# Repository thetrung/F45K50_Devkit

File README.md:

PIC18-F45K50-DevKit / Mini-USB
===================================
Basic USB Type-B DevKit I made to learn about **PIC18F45K50** microcontroller.

- **PIC18F45K50-I/MV** will be used specifically as UQFN-40(5x5) instead DIP-40 package in previous THT version.

I actually tried to put all SMD components on front side only. Used Mini-USB instead of USB-B in previous THT version. So this isn't optimized by any mean, just simply a practice to experience what SMD PCB Design look like & what challenge compare to THT ? Although initial goal was same size to a DIP-40. But Port hints are so valuable to remove.

### 1. Basic functionality :
- USB-powered 5V supply.
- USB-HID controllable with PIC18F45k50 with D+/D- pins.
- Reset Button -> Trigger MLCR-pin pull-down -> GND.
- Programming/Debugging with PICKIT-3 via ICSP pins.
- 5 pluggable PORTS : RA, RB, RC, RD, RE.
- LED at RD0 for Blink Test.

### NOTE :
- Fixed critical issues on MCLR pin, Reset Button, ICSP..
- Should only take this design as references to parts.
- No longer update/fix bugs anymore as I move-on to new designs ( with less flaws ).

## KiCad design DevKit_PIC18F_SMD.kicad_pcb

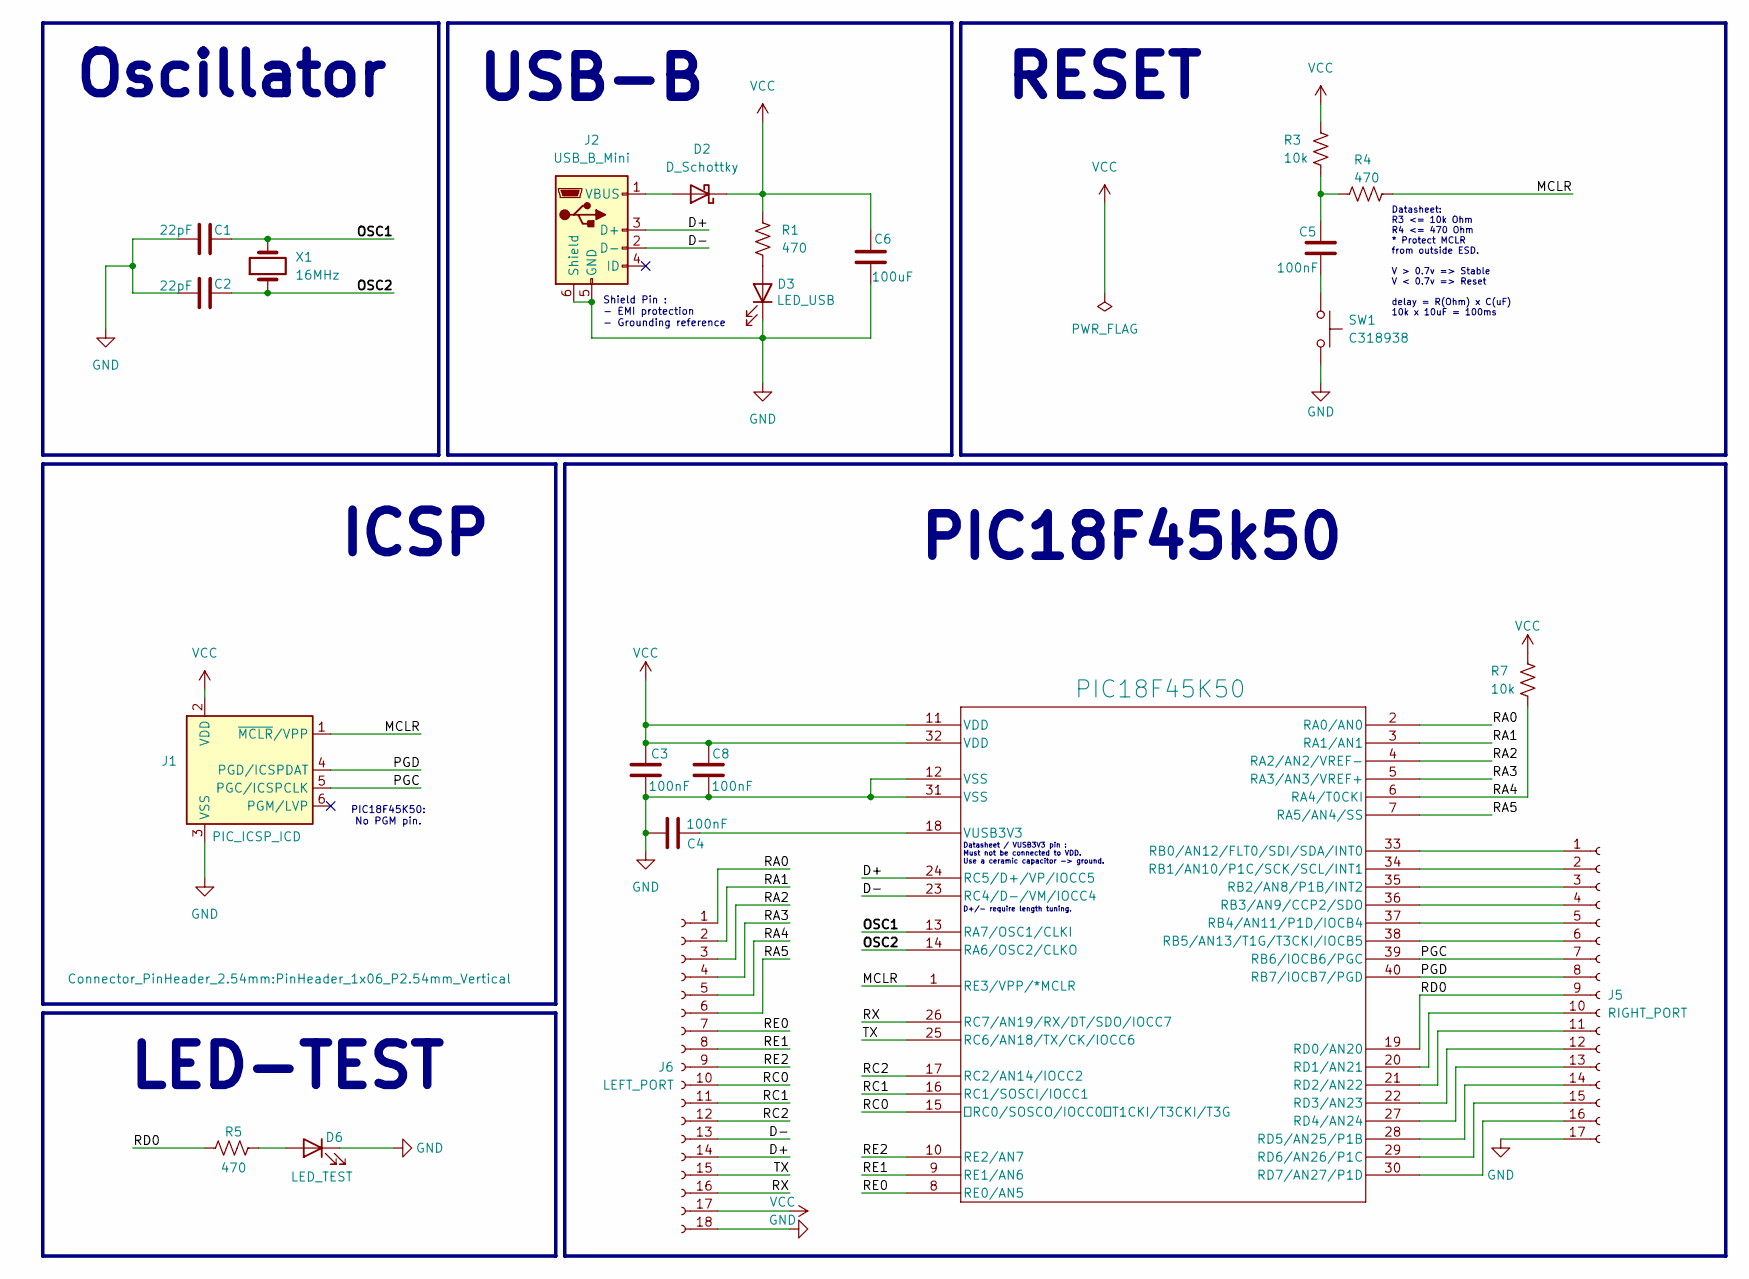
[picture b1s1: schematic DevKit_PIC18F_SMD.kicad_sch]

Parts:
C1, C2: 22pF; C_0805_2012Metric
C3, C4, C5, C8: 100nF; C_1206_3216Metric
C6: 100uF; C_1206_3216Metric
D2: D_Schottky; D_0603_1608Metric
D3: LED_USB; LED_0805_2012Metric
D6: LED_TEST; LED_0805_2012Metric
J1: PIC_ICSP_ICD; PinHeader_1x06_P2.54mm_Vertical
J2: USB_B_Mini; USB_Mini-B_Tensility_54-00023_Vertical
J5: RIGHT_PORT; PinHeader_1x17_P2.54mm_Vertical
J6: LEFT_PORT; PinHeader_1x18_P2.54mm_Vertical
PIC18F45K50: PIC18F45K50-I/MV; QFN-40-1EP_5x5mm_P0.4mm_EP3.6x3.6mm
R1, R4, R5: 470; R_0805_2012Metric
R3, R7: 10k; R_1206_3216Metric
SW1: C318938; SW_SPST_SKQG_WithStem
X1: 16MHz; Crystal_SMD_2520-4Pin_2.5x2.0mm

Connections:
/D+: J2.3 (D+), J6.14, PIC18F45K50.24 (RC5/D+/VP/IOCC5)
/D-: J2.2 (D-), J6.13, PIC18F45K50.23 (RC4/D-/VM/IOCC4)
/MCLR: J1.1 (~MCLR/VPP), PIC18F45K50.1 (RE3/VPP/*MCLR), R4.1
/OSC1: C1.1, PIC18F45K50.13 (RA7/OSC1/CLKI), X1.2
/OSC2: C2.1, PIC18F45K50.14 (RA6/OSC2/CLKO), X1.1
/PGC: J1.5 (PGC/ICSPCLK), J5.7, PIC18F45K50.39 (RB6/IOCB6/PGC)
/PGD: J1.4 (PGD/ICSPDAT), J5.8, PIC18F45K50.40 (RB7/IOCB7/PGD)
/RA0: J6.1, PIC18F45K50.2 (RA0/AN0)
/RA1: J6.2, PIC18F45K50.3 (RA1/AN1)
/RA2: J6.3, PIC18F45K50.4 (RA2/AN2/VREF-)
/RA3: J6.4, PIC18F45K50.5 (RA3/AN3/VREF+)
/RA4: J6.5, PIC18F45K50.6 (RA4/T0CKI), R7.2
/RA5: J6.6, PIC18F45K50.7 (RA5/AN4/SS)
/RC0: J6.10, PIC18F45K50.15 (RC0/SOSCO/IOCC0 T1CKI/T3CKI/T3G)
/RC1: J6.11, PIC18F45K50.16 (RC1/SOSCI/IOCC1)
/RC2: J6.12, PIC18F45K50.17 (RC2/AN14/IOCC2)
/RD0: J5.9, PIC18F45K50.19 (RD0/AN20), R5.1
/RE0: J6.7, PIC18F45K50.8 (RE0/AN5)
/RE1: J6.8, PIC18F45K50.9 (RE1/AN6)
/RE2: J6.9, PIC18F45K50.10 (RE2/AN7)
/RX: J6.16, PIC18F45K50.26 (RC7/AN19/RX/DT/SDO/IOCC7)
/TX: J6.15, PIC18F45K50.25 (RC6/AN18/TX/CK/IOCC6)
GND: C1.2, C2.2, C3.2, C4.1, C6.1, C8.2, D3.1 (K), D6.1 (K), J1.3 (VSS), J2.5 (GND), J2.6 (Shield), J5.17, J6.18, PIC18F45K50.12 (VSS), PIC18F45K50.31 (VSS), SW1.2
unnamed: C5.1, SW1.1
unnamed: C5.2, R3.2, R4.2
unnamed: D2.2 (A), J2.1 (VBUS)
unnamed: D3.2 (A), R1.2
unnamed: D6.2 (A), R5.2
unnamed: J5.1, PIC18F45K50.33 (RB0/AN12/FLT0/SDI/SDA/INT0)
unnamed: J5.2, PIC18F45K50.34 (RB1/AN10/P1C/SCK/SCL/INT1)
unnamed: J5.3, PIC18F45K50.35 (RB2/AN8/P1B/INT2)
unnamed: J5.4, PIC18F45K50.36 (RB3/AN9/CCP2/SDO)
unnamed: J5.5, PIC18F45K50.37 (RB4/AN11/P1D/IOCB4)
unnamed: J5.6, PIC18F45K50.38 (RB5/AN13/T1G/T3CKI/IOCB5)
unnamed: J5.10, PIC18F45K50.20 (RD1/AN21)
unnamed: J5.11, PIC18F45K50.21 (RD2/AN22)
unnamed: J5.12, PIC18F45K50.22 (RD3/AN23)
unnamed: J5.13, PIC18F45K50.27 (RD4/AN24)
unnamed: J5.14, PIC18F45K50.28 (RD5/AN25/P1B)
unnamed: J5.15, PIC18F45K50.29 (RD6/AN26/P1C)
unnamed: J5.16, PIC18F45K50.30 (RD7/AN27/P1D)
unnamed: C4.2, PIC18F45K50.18 (VUSB3V3)
VCC: C3.1, C6.2, C8.1, D2.1 (K), J1.2 (VDD), J6.17, PIC18F45K50.11 (VDD), PIC18F45K50.32 (VDD), R1.1, R3.1, R7.1

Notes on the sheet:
RESET
USB-B
D+/- require length tuning.
ICSP
Shield Pin : - EMI protection - Grounding reference
Datasheet / VUSB3V3 pin : Must not be connected to VDD. Use a ceramic capacitor -> ground.
LED-TEST
Datasheet: R3 <= 10k Ohm R4 <= 470 Ohm * Protect MCLR from outside ESD. V > 0.7v => Stable V < 0.7v => Reset delay = R(Ohm) x C(uF) 10k x 10uF = 100ms
Oscillator
PIC18F45K50: No PGM pin.
PIC18F45k50

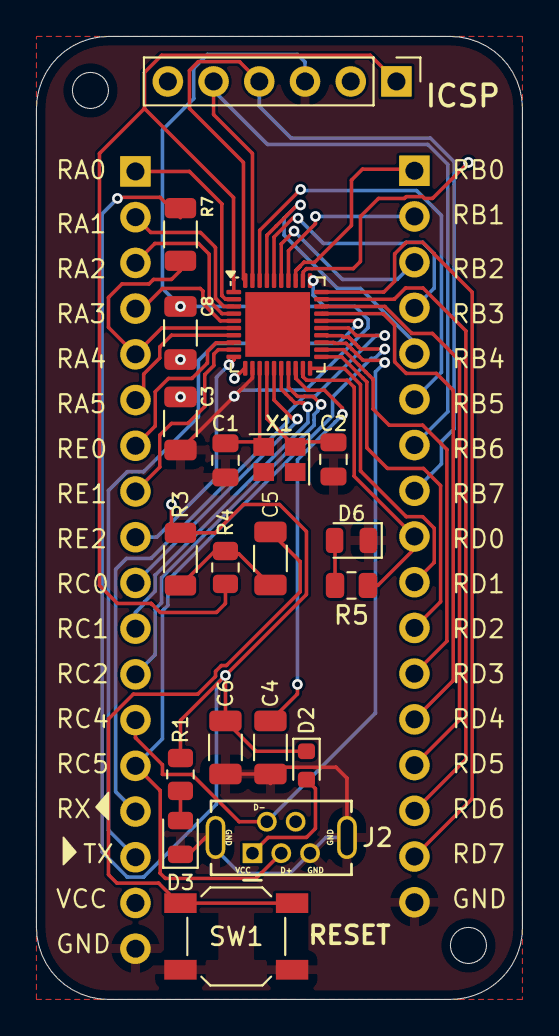
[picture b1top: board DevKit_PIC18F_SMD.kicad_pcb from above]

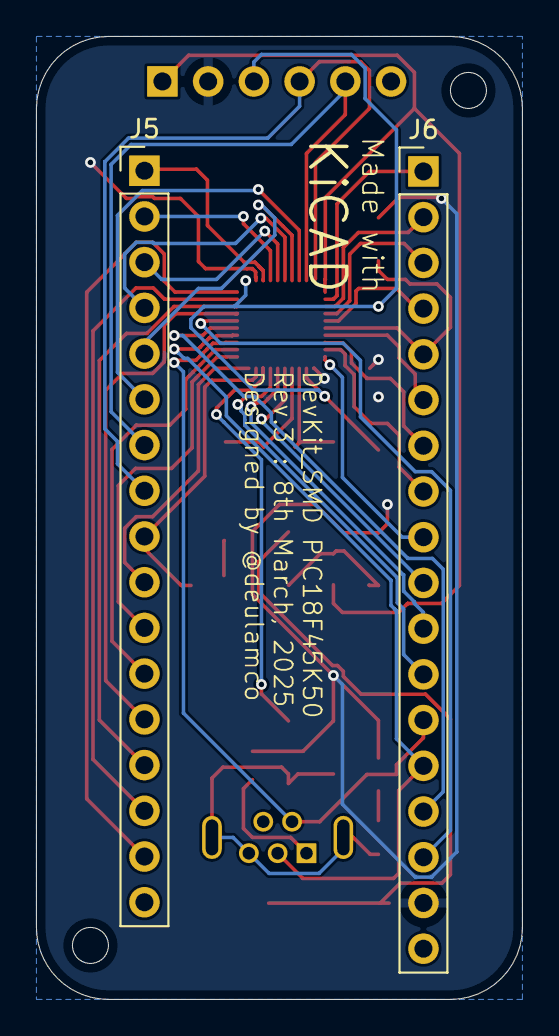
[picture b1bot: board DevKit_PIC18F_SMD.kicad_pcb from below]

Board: 2 copper layers, 27.0 x 53.5 mm, 22 parts (2 on the bottom side), 43 nets.

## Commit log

2025-05-01 Fix Reset Button, ICSP... etc.
2025-05-02 update images
